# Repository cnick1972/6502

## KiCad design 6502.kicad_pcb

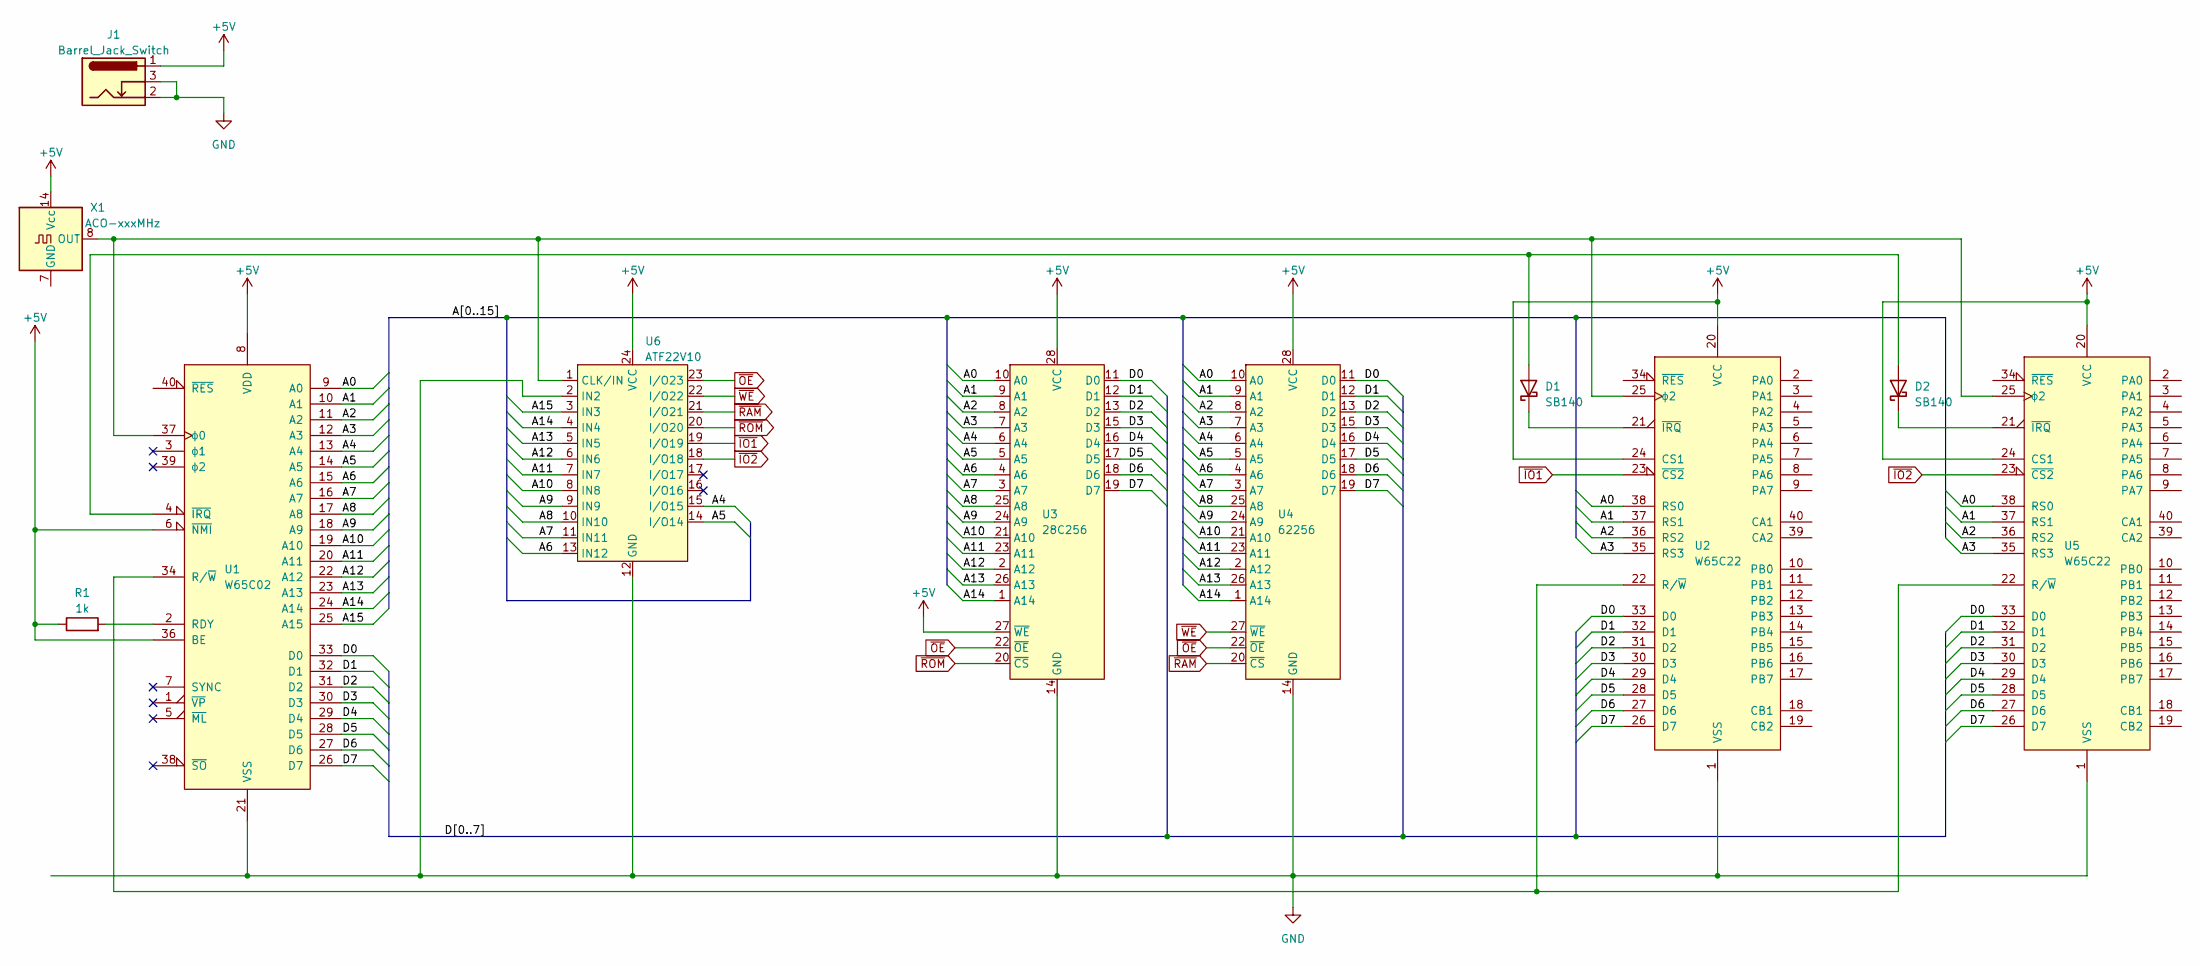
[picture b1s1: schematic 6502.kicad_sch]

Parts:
D1, D2: SB140; D_DO-41_SOD81_P10.16mm_Horizontal
J1: Barrel_Jack_Switch; BarrelJack_Wuerth_6941xx301002
R1: 1k; R_Axial_DIN0207_L6.3mm_D2.5mm_P7.62mm_Horizontal
U1: W65C02; DIP-40_W15.24mm_Socket
U2, U5: W65C22; DIP-40_W15.24mm_Socket
U3: 28C256; DIP-28_W15.24mm_Socket
U4: 62256; DIP-28_W15.24mm_Socket
U6: ATF22V10; DIP-24_W7.62mm_Socket
X1: ACO-xxxMHz; Oscillator_DIP-14

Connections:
+5V: J1.1, R1.1, U1.6 (~NMI), U1.8 (VDD), U1.36 (BE), U2.20 (VCC), U2.24 (CS1), U3.27 (~WE), U3.28 (VCC), U4.28 (VCC), U5.20 (VCC), U5.24 (CS1), U6.24 (VCC), X1.14 (Vcc)
/A0: U1.9 (A0), U2.38 (RS0), U3.10 (A0), U4.10 (A0), U5.38 (RS0)
/A1: U1.10 (A1), U2.37 (RS1), U3.9 (A1), U4.9 (A1), U5.37 (RS1)
/A2: U1.11 (A2), U2.36 (RS2), U3.8 (A2), U4.8 (A2), U5.36 (RS2)
/A3: U1.12 (A3), U2.35 (RS3), U3.7 (A3), U4.7 (A3), U5.35 (RS3)
/A4: U1.13 (A4), U3.6 (A4), U4.6 (A4), U6.15 (I/O15)
/A5: U1.14 (A5), U3.5 (A5), U4.5 (A5), U6.14 (I/O14)
/A6: U1.15 (A6), U3.4 (A6), U4.4 (A6), U6.13 (IN12)
/A7: U1.16 (A7), U3.3 (A7), U4.3 (A7), U6.11 (IN11)
/A8: U1.17 (A8), U3.25 (A8), U4.25 (A8), U6.10 (IN10)
/A9: U1.18 (A9), U3.24 (A9), U4.24 (A9), U6.9 (IN9)
/A10: U1.19 (A10), U3.21 (A10), U4.21 (A10), U6.8 (IN8)
/A11: U1.20 (A11), U3.23 (A11), U4.23 (A11), U6.7 (IN7)
/A12: U1.22 (A12), U3.2 (A12), U4.2 (A12), U6.6 (IN6)
/A13: U1.23 (A13), U3.26 (A13), U4.26 (A13), U6.5 (IN5)
/A14: U1.24 (A14), U3.1 (A14), U4.1 (A14), U6.4 (IN4)
/A15: U1.25 (A15), U6.3 (IN3)
/D0: U1.33 (D0), U2.33 (D0), U3.11 (D0), U4.11 (D0), U5.33 (D0)
/D1: U1.32 (D1), U2.32 (D1), U3.12 (D1), U4.12 (D1), U5.32 (D1)
/D2: U1.31 (D2), U2.31 (D2), U3.13 (D2), U4.13 (D2), U5.31 (D2)
/D3: U1.30 (D3), U2.30 (D3), U3.15 (D3), U4.15 (D3), U5.30 (D3)
/D4: U1.29 (D4), U2.29 (D4), U3.16 (D4), U4.16 (D4), U5.29 (D4)
/D5: U1.28 (D5), U2.28 (D5), U3.17 (D5), U4.17 (D5), U5.28 (D5)
/D6: U1.27 (D6), U2.27 (D6), U3.18 (D6), U4.18 (D6), U5.27 (D6)
/D7: U1.26 (D7), U2.26 (D7), U3.19 (D7), U4.19 (D7), U5.26 (D7)
GND: J1.2, J1.3, U1.21 (VSS), U2.1 (VSS), U3.14 (GND), U4.14 (GND), U5.1 (VSS), U6.2 (IN2), U6.12 (GND)
unnamed: D1.2 (A), D2.2 (A), U1.4 (~IRQ)
unnamed: D1.1 (K), U2.21 (~IRQ)
unnamed: D2.1 (K), U5.21 (~IRQ)
unnamed: R1.2, U1.2 (RDY)
unnamed: U1.34 (R/~W), U2.22 (R/~W), U5.22 (R/~W)
unnamed: U1.37 (ϕ0), U2.25 (ϕ2), U5.25 (ϕ2), U6.1 (CLK/IN), X1.8 (OUT)
~IO1: U2.23 (~CS2), U6.19 (I/O19)
~IO2: U5.23 (~CS2), U6.18 (I/O18)
~OE: U3.22 (~OE), U4.22 (~OE), U6.23 (I/O23)
~RAM: U4.20 (~CS), U6.21 (I/O21)
~ROM: U3.20 (~CS), U6.20 (I/O20)
~WE: U4.27 (~WE), U6.22 (I/O22)

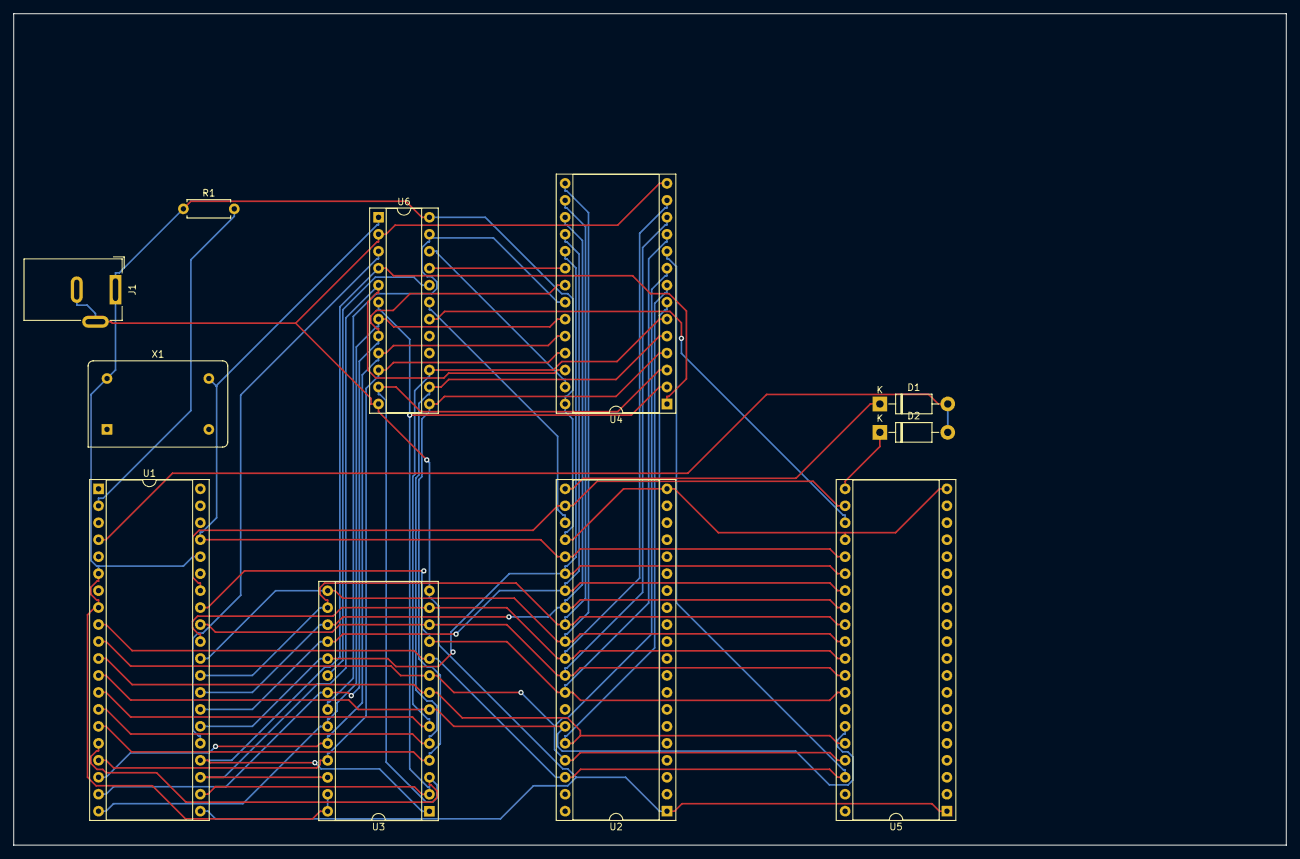
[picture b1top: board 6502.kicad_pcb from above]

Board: 2 copper layers, 190.5 x 124.5 mm, 11 parts (0 on the bottom side), 38 nets.

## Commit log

2023-04-16 First commit of 6502 pcb project
2023-04-16 Updated schematic design files
